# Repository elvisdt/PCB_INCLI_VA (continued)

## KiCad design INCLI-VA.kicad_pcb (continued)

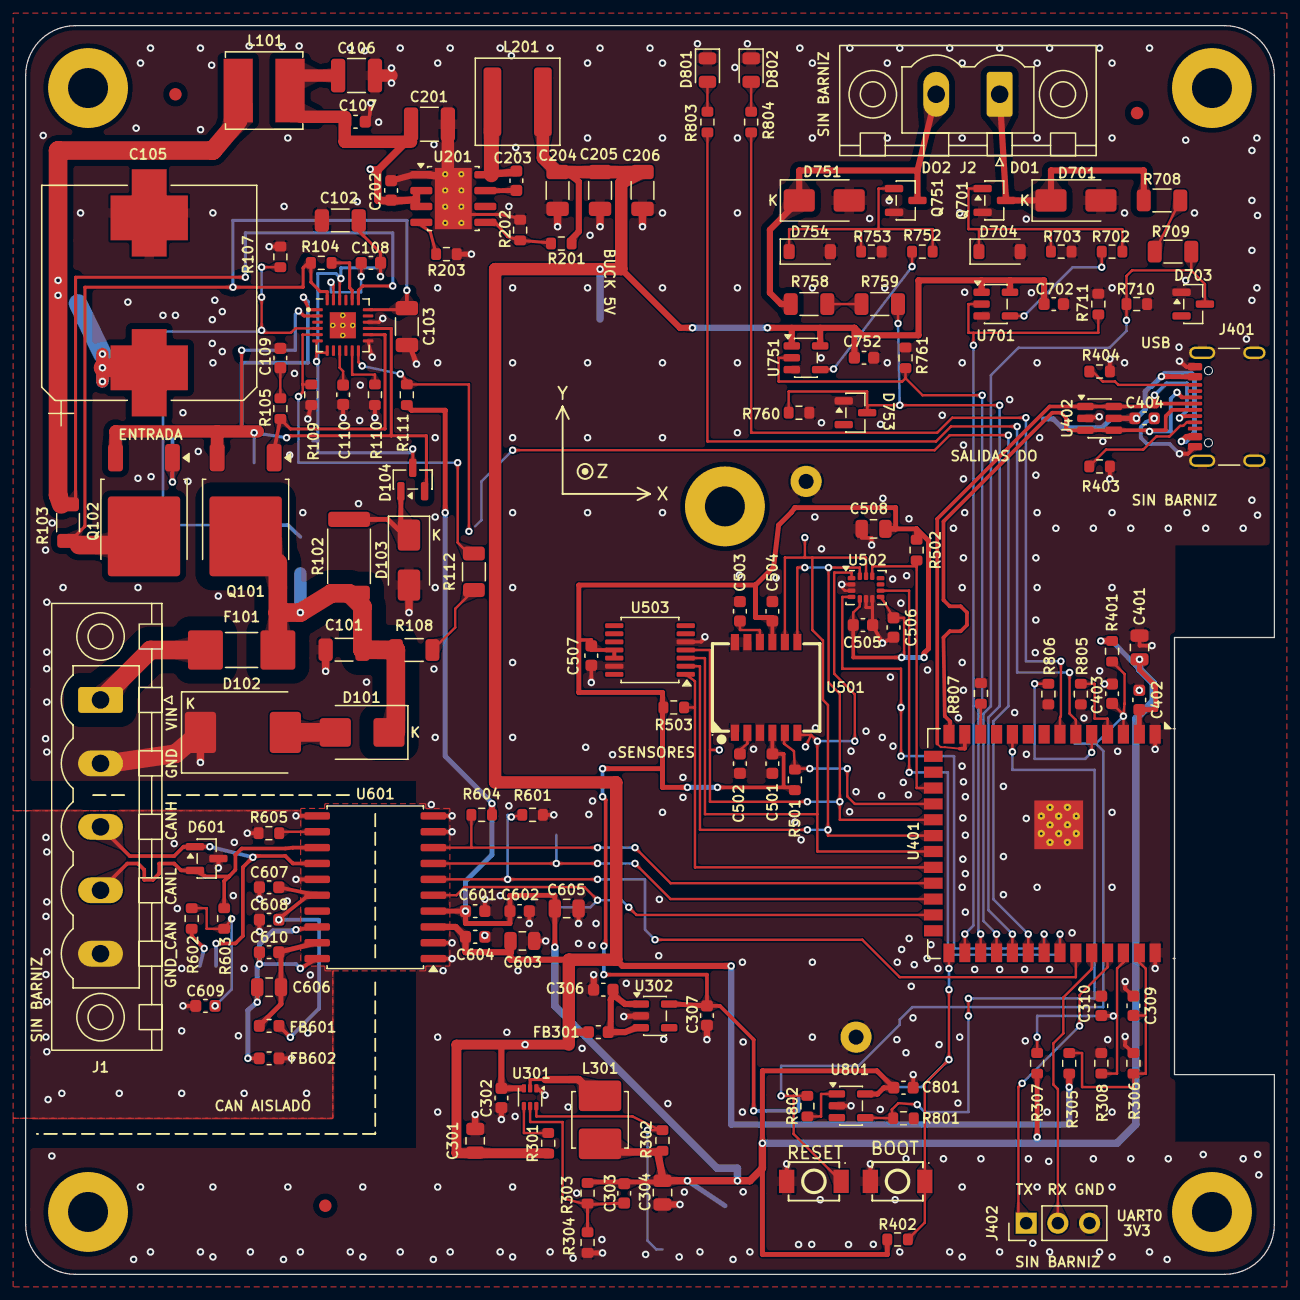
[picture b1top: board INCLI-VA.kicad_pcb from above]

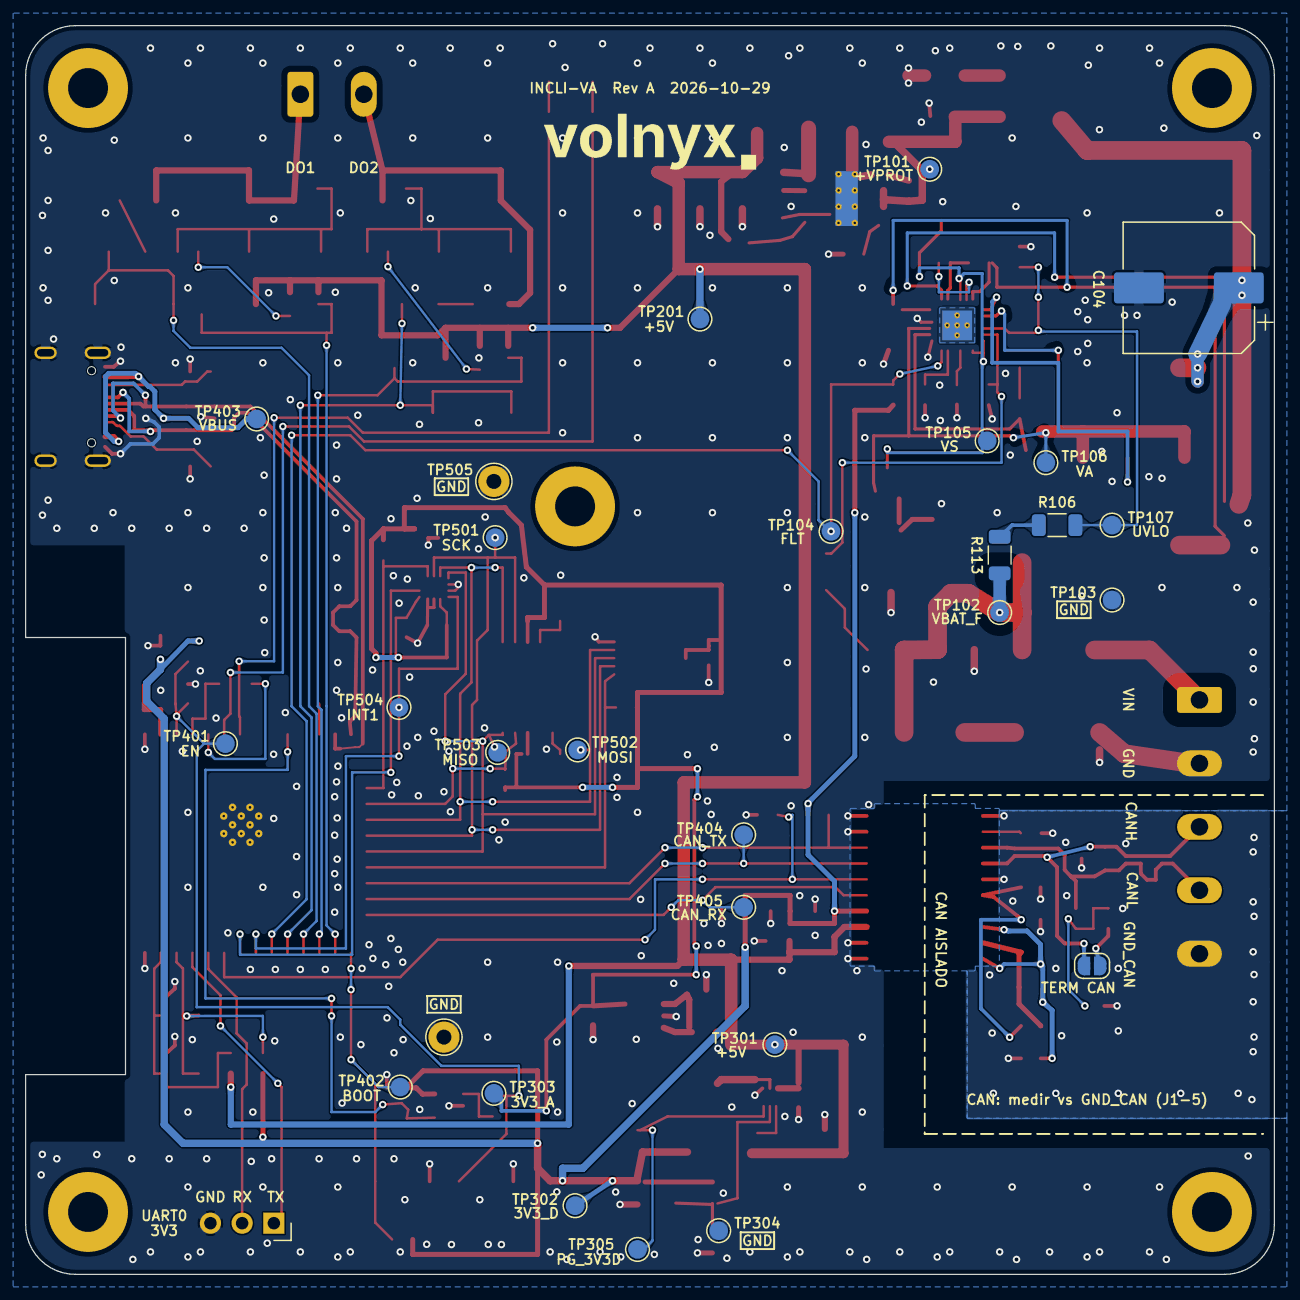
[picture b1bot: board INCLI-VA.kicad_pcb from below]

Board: 2 copper layers, 100.0 x 100.0 mm, 180 parts (29 on the bottom side), 89 nets.

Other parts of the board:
LOGO1: Logo_Volnyx_Wordmark

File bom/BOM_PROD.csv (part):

Comment,Designator,Footprint,Qty,MPN,Manufacturer,LCSC,JLC_Type,JLC_Stock,LCSC_Stock,Price_10_USD,Supplier,Assembly,Status,Orig_MPN,Orig_LCSC,Notes
100nF,C101,C_1206_3216Metric,1,CGA5L4X7T2W104K160AA,TDK,,,,,0.7901 (ref. LCSC),DigiKey/Mouser,consigna JLC o mano,"not at JLC, DigiKey/Mouser, checked 2026-10-30",,C3887150,PROD mantiene el AEC-Q200 original (JLC/LCSC stock 1); el sustituto sin AEC-Q200 es solo para PROTO
1uF,"C102,C103",C_1206_3216Metric,2,CL31B105KCHNNNE,Samsung,C13832,ext,347728,261400,0.0650,JLC,JLC,"substitute CL31B105KCHNNNE for CGA5L2X7R2A105K160AA accepted 2026-10-30, JLC ext",CGA5L2X7R2A105K160AA,C2168321,"original stock 0; 1uF 100V X7R 1206, no AEC-Q200"
47uF,C104,CP_Elec_10x10,1,EEE-HA2A470UP,Panasonic,,,,,0.3957 (ref. LCSC),DigiKey/Mouser,consigna JLC o mano,"not at JLC, DigiKey/Mouser, checked 2026-10-30",,C344077,PROD mantiene el AEC-Q200 original (JLC/LCSC stock 1); el sustituto sin AEC-Q200 es solo para PROTO
1000uF 50V,C105,CP_Elec_Panasonic_J16_VibProof,1,EEE-FK1H102AV,Panasonic,,,,,0.8694 (ref. LCSC),DigiKey/Mouser,consigna JLC o mano,"not at JLC, DigiKey/Mouser, checked 2026-10-30",,C2164039,JLC/LCSC stock 0 (tambien Alt_MPN EEE-FK1H102AM)
10uF,C106,C_1210_3225Metric,1,CL32B106KBJNNNE,Samsung,C138687,ext,101468,9473,0.2610,JLC,JLC,"substitute CL32B106KBJNNNE for GCM32ER71H106KA12L accepted 2026-10-30, JLC ext",GCM32ER71H106KA12L,,original no listado en JLC; 10uF 50V X7R 1210. Alternativa automotriz: C126612 GCM32EC71H106KA03L (X7S)
100nF,"C107,C108,C109,C202,C203,C302,C309,C310,C402,C404,C501,C502,C503,C504,C505,C506,C507,C602,C604,C608,C702,C752,C801",C_0603_1608Metric,23,GCM188R72A104KA64D,Murata,C415406,ext,15215,10480,0.0637,JLC,JLC,"consolidado 2026-10-30: un solo MPN de 100 nF, 100 V X7R AEC-Q200",,,"100nF 50V X7R 0603, no AEC-Q200"
68nF,C110,C_0603_1608Metric,1,CL10B683KB8NNNC,Samsung,C31658,pref,150525,115600,0.0190 (MOQ 50),JLC,JLC,"substitute CL10B683KB8NNNC for GCM188R71H683KA57D accepted 2026-10-30, JLC pref",GCM188R71H683KA57D,C380380,original stock 0; 68nF 50V X7R 0603 (JLC pref)
4.7uF,C201,C_1210_3225Metric,1,CGA6M3X7S2A475K200AB,TDK,,,,,1.5766 (ref. LCSC),DigiKey/Mouser,consigna JLC o mano,"not at JLC, DigiKey/Mouser, checked 2026-10-30",,C2168848,PROD mantiene el AEC-Q200 original (JLC/LCSC stock 0); el sustituto sin AEC-Q200 es solo para PROTO
22uF,"C204,C205,C206",C_1206_3216Metric,3,GCM31CR71A226KE02L,Murata,C126598,ext,13053,11240,0.3296,JLC,JLC,"JLC ext, verified 2026-10-30",,,
10uF,"C301,C508,C603,C605,C606",C_0805_2012Metric,5,GCM21BR71A106KE22L,Murata,C126586,ext,9971,0,0.1029,JLC,JLC,"JLC ext, verified 2026-10-30",,,
10pF,C303,C_0603_1608Metric,1,CL10C100JB8NNNC,Samsung,C1634,basic,1212785,100,0.0061 (MOQ 100),JLC,JLC,"JLC basic (swap from GCM1885C1H100JA16D), verified 2026-10-30",GCM1885C1H100JA16D,C126542,original stock 0; 10pF 50V C0G 0603
22uF,"C304,C401",C_0805_2012Metric,2,GRM21BZ71A226ME15L,Murata,C907991,ext,166294,140195,0.3744,JLC,JLC,"JLC ext, verified 2026-10-30",,,
1uF,"C306,C307,C403",C_0603_1608Metric,3,GCM188R71C105KA64D,Murata,C161212,ext,33722,18280,0.0383 (MOQ 20),JLC,JLC,"JLC ext, verified 2026-10-30",,,
10nF,"C601,C607",C_0603_1608Metric,2,0603B103K500NT,FH,C57112,basic,5628260,28450,0.0098 (MOQ 50),JLC,JLC,"JLC basic (swap from GCM188R71H103KA37D), verified 2026-10-30",GCM188R71H103KA37D,C85863,"10nF 50V X7R 0603, no AEC-Q200"
4.7nF,C609,C_0603_1608Metric,1,GCM188R72A472KA37D,Murata,C426631,ext,16111,16100,0.0288 (MOQ 20),JLC,JLC,"JLC ext, verified 2026-10-30",,,
220nF,C610,C_0603_1608Metric,1,CL10B224KA8NNNC,Samsung,C21120,basic,1011962,394350,0.0094 (MOQ 50),JLC,JLC,"JLC basic (swap from GCM188R71E224KA55D), verified 2026-10-30",GCM188R71E224KA55D,C161217,"220nF 25V X7R 0603, no AEC-Q200"
ES2G,D101,D_SMB,1,ES2G-E3/52T,Vishay,C2927419,ext,8924,8920,0.1781,JLC,JLC,"JLC ext, verified 2026-10-30",,,
SMCJ33A,D102,D_SMC,1,SMCJ33A,Littelfuse,C438109,ext,26629,26625,0.1049,JLC,JLC,"JLC ext, verified 2026-10-30",,,
SMAJ51A,D103,D_SMA,1,SMAJ51A,Littelfuse,C366557,ext,5525,5520,0.0314 (MOQ 20),JLC,JLC,"JLC ext, verified 2026-10-30",,,
BAV23C,D104,SOT-23,1,"BAV23C,215",Nexperia,C282370,ext,0,0,"0.1158 (ref. LCSC, MOQ 5)",DigiKey/Mouser,consigna JLC o mano,"not at JLC/LCSC (stock 0), DigiKey/Mouser, checked 2026-10-30",,,rc6 R-02 (D1 de TI fig. 8-1 dentro de D104); PROD automotriz: evaluar BAV23CQ
SMAJ58A,"D701,D751",D_SMA,2,SMAJ58A,Littelfuse,C123816,ext,15859,15840,0.0456 (MOQ 20),JLC,JLC,"JLC ext, verified 2026-10-30",,,
BZX84-C3V3,"D703,D753",SOT-23,2,"BZX84-C3V3,215",Nexperia,C85087,ext,28154,28150,0.0180 (MOQ 50),JLC,JLC,"JLC ext, verified 2026-10-30",,,
12V,"D704,D754",D_SOD-123,2,MMSZ5242B-7-F,Diodes Incorporated,C500776,ext,97152,97150,0.0450,JLC,JLC,"JLC ext, verified 2026-10-30",,,
2A 250VDC,F101,Fuse_Bourns_SF-2410,1,SF-2410FPA200W-2,Bourns,,,,,1.0524 (ref. LCSC),DigiKey/Mouser,consigna JLC o mano,"not at JLC, DigiKey/Mouser, checked 2026-10-30",,C3159902,"JLC/LCSC stock 0; sustituto AEM MF2410 rechazado (proteccion de entrada, el prototipo valida el diseno de produccion)"
220R@100MHz,FB301,L_0603_1608Metric,1,BLM18PG221SN1D,Murata,C80165,ext,243305,235750,0.0149 (MOQ 50),JLC,JLC,"JLC ext, verified 2026-10-30",,,
1.8k@100MHz,"FB601,FB602",L_0603_1608Metric,2,BLM18BD182SN1D,Murata,C113020,ext,5170,5160,0.0362 (MOQ 20),JLC,JLC,"JLC ext, verified 2026-10-30",,,
"MSTBV 2,5/5-GF-5,08",J1,"PhoenixContact_MSTBV_2,5_5-GF-5,08_1x05_P5.08mm_Vertical_ThreadedFlange",1,1777109,Phoenix Contact,C7164734,ext,327,317,0.9724,LCSC,mano,"JLC ext, verified 2026-10-30",,,
"MSTBV 2,5/2-GF-5,08",J2,"PhoenixContact_MSTBV_2,5_2-GF-5,08_1x02_P5.08mm_Vertical_ThreadedFlange",1,1777073,Phoenix Contact,C480552,ext,837,835,1.1001,LCSC,mano,"JLC ext, verified 2026-10-30",,,
USB4105-GF-A,J401,USB_C_Receptacle_GCT_USB4105-xx-A_16P_TopMnt_Horizontal,1,USB4105-GF-A,GCT,C3020560,ext,3189,413,1.1001,LCSC,mano,"JLC ext, verified 2026-10-30",,,
UART0,J402,PinHeader_1x03_P2.54mm_Vertical,1,2.54-1*3PPin,BOOMELE,C49257,ext,151423,151440,0.0286 (MOQ 20),LCSC,mano,"substitute 2.54-1*3PPin for 61300311121 accepted 2026-10-30, JLC ext",61300311121,C2915006,"Wurth 61300311121 solo en JLC, no en lcsc.com; tira 1x3 2.54 mm generica"
10uH,L101,L_Bourns_SRN6045TA,1,SRN6045TA-100M,Bourns,C2046332,ext,6156,6045,0.2544,JLC,JLC,"JLC ext, verified 2026-10-30",,,
33uH,L201,L_Coilcraft_XAL6060-XXX,1,XAL6060-333MEC,Coilcraft,,,,,2.8281 (ref. LCSC),DigiKey/Mouser,consigna JLC o mano,"not at JLC, DigiKey/Mouser, checked 2026-10-30",,C5119929,JLC/LCSC stock 0; sin equivalente 33uH en la misma huella
1uH,L301,L_Coilcraft_XAL4020_HandSolder,1,XAL4020-102MEC,Coilcraft,C4555951,ext,7626,7626,4.2523,JLC,JLC,"JLC ext, verified 2026-10-30",,,
STD18NF25,Q101,TO-252-2,1,STD18NF25,STMicroelectronics,,,,,5.3743 (ref. LCSC),DigiKey/Mouser,consigna JLC o mano,"not at JLC, DigiKey/Mouser, checked 2026-10-30",,C183634,JLC/LCSC stock 0; sustituto AOD458 rechazado (proteccion de entrada)
IPD30N10S3L-34,Q102,TO-252-2,1,IPD30N10S3L34ATMA1,Infineon,,,,,1.2069 (ref. LCSC),DigiKey/Mouser,consigna JLC o mano,"not at JLC, DigiKey/Mouser, checked 2026-10-30",,C148263,JLC/LCSC stock 0; sustituto IRLR3110Z rechazado (proteccion de entrada)
DMN10H220LQ,"Q701,Q751",SOT-23,2,DMN10H220LQ-7,Diodes Incorporated,C5260572,ext,4738,4595,0.2997,JLC,JLC,"JLC ext, verified 2026-10-30",,,
10k,R102,R_2512_6332Metric,1,AC2512FK-0710KL,Yageo,C469651,ext,1508,1505,0.0933,JLC,JLC,"JLC ext, verified 2026-10-30",,,
10m,R103,R_1206_3216Metric,1,ERJ-8BWFR010V,Panasonic,C2076185,ext,5332,4125,0.1219,JLC,JLC,"JLC ext, verified 2026-10-30",,,
49.9,R104,R_0603_1608Metric,1,0603WAF499JT5E,UNI-ROYAL,C23185,basic,1388908,411400,0.0021 (MOQ 100),JLC,JLC,"JLC basic (swap from AC0603FR-0749R9L), verified 2026-10-30",AC0603FR-0749R9L,C144653,1% 0603
100,R105,R_0603_1608Metric,1,0603WAF1000T5E,UNI-ROYAL,C22775,basic,9522722,1107900,0.0024 (MOQ 100),JLC,JLC,"JLC basic (swap from AC0603FR-07100RL), verified 2026-10-30",AC0603FR-07100RL,C125923,1% 0603
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
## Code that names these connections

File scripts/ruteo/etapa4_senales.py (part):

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P = '/10_power_input/'
# SW: pin 3 -> R106.1 recto al oeste.
T(P+'SW', .2, [(123.375, 73.75), (120.4, 73.75)])
# UVLO: pin 4 -> oeste por el hueco R106/C109 -> x118.9 -> R106.2; salto B.Cu
# bajo la Kelvin C_ID (y70.95) hasta R107.1.
T(P+'UVLO', .2, [(123.375, 74.25), (121.6, 74.25), (121.25, 74.6), (118.9, 74.6), (118.9, 71.745), (120.4, 71.745)])
V(P+'UVLO', (118.9, 71.745))
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# TMR, ILIM.
T(P+'TMR', .2, [(125.15, 76.025), (125.15, 77.4), (125.425, 77.675), (125.425, 78.785)])
T(P+'ILIM', .2, [(126.15, 76.025), (126.15, 77.95), (127.975, 77.95), (127.975, 78.735)])
# FLT: pin 12 -> via -> B.Cu bajo HGATE/VA -> R111.2 -> TP104.
FLT = '/PWR_FLT_N'
T(FLT, .2, [(126.65, 76.025), (126.65, 76.95), (126.95, 77.25)])
V(FLT, (126.95, 77.25))
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V(VS, (128.42, 70.1))
T(VS, .25, [(128.42, 70.1), (128.425, 69.0)])
T(VS, .25, [(128.425, 69.0), (128.425, 68.2), (126.675, 66.45), (126.675, 65.6)])
# CAP: pin 23 -> via -> U por B.Cu y71.35 -> via -> C108.1.
CAP = P+'CAP'
T(CAP, .2, [(124.65, 71.975), (124.65, 70.75), (124.45, 70.55)])
V(CAP, (124.45, 70.55))
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T('/VAR_ID1', .2, [(180.8, 102.7), (181.9, 102.705)])

# ---------------------------------------------- Bus bajo el modulo y USB ----
# Pines 28-32 (DO1_EN, DO2_EN, DO1_DIAG, DO2_DIAG, PWR_FLT_N) bajan a B.Cu en el
# lado interior del pad y suben por carriles x175.9-177.5; LED_G/LED_R se suman
# en el bolsillo norte. Todos cruzan el par USB una sola vez, por B.Cu.
bus = [('/DO1_EN', 175.21), ('/DO2_EN', 176.48), ('/DO1_DIAG', 177.75), ('/DO2_DIAG', 179.02), (FLT, 180.29)]
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M('R502', (171.35, 92.0), 270)
M('TP504', (170.1, 104.6), 180)

# --- CS_IMU: pin 17 -> x171.35 -> norte -> pad 12; R502 en el camino ---
CSI = '/CS_IMU'
T(CSI, .2, [(172.69, 111.055), (171.35, 111.055), (171.35, 93.3), (167.8, 93.3), (167.8, 94.0875)])
T(CSI, .2, [(171.35, 93.3), (171.35, 92.825)])
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T(SCK, .2, [(162.6, 114.4), (164.25, 114.4)], B); V(SCK, (164.25, 114.4))                                         # cruce J_e (via en la banda)
T(CSR, .2, [(152.8625, 101.95), (153.6, 102.5), (153.6, 117.405), (172.69, 117.405)])
T(CSR, .2, [(152.725, 104.6), (153.6, 104.6)])
# CS_INC: pin 18 -> salto bajo MOSI/SCK/MISO (J_c) -> R501 -> U501.5
T(CSN, .2, [(172.69, 112.325), (166.4, 112.325), (165.8, 111.725), (165.8, 109.5)]); V(CSN, (165.8, 109.5))
T(CSN, .2, [(165.8, 109.5), (162.8, 109.5)], B); V(CSN, (162.8, 109.5))
T(CSN, .2, [(162.8, 109.5), (161.6, 109.5), (161.6, 109.575)])
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
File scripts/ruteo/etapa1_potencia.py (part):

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    'VP': '+VPROT', 'G': 'GND_VEH', 'SW': '/20_buck_5v/BUCK_SW', 'BOOT': '/20_buck_5v/BUCK_BOOT',
    'FB': '/20_buck_5v/BUCK_FB', 'RT': '/20_buck_5v/BUCK_RT', 'P5': '+5V_VEH', 'A1': 'Net-(D103-A1)',
    'SW3': 'Net-(U301-SW)', 'FB3': 'Net-(U301-FB)', 'EN3': 'Net-(U301-EN)', 'UEN': 'Net-(U302-EN)',
    'P3D': '+3V3_D', 'P3A': '+3V3_A', 'PG3': '/30_regulation/PG_3V3D',
}


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T('VOUT', 1.0, [(106.15, 76.3), (106.15, 78.5)], B)
T('VOUT', 1.5, [(106.15, 76.3), (104.2, 72.25)], B)

# Kelvin de R103: dos pistas separadas desde los pads hasta U101 (CSP via R104 y CS- pin 19).
T('VOUT', 0.25, [(104.0, 88.1), (104.0, 70.15), (117.6, 70.15)])
V('VOUT', 117.6, 70.15)
T('CID', 0.25, [(104.0, 90.85), (104.75, 90.1), (104.75, 70.95), (122.3, 70.95), (122.3, 69.4), (122.6, 69.0)])
V('CID', 116.6, 70.95)
# CS- (pin 19): F.Cu corto hasta una via y arco por B.Cu hasta la Kelvin VOUT.
T('VOUT', 0.25, [(126.65, 71.9), (126.65, 71.2), (127.0, 70.85), (129.4, 70.85)])
V('VOUT', 129.4, 70.85)
T('VOUT', 0.25, [(129.4, 70.85), (129.4, 66.6), (117.6, 66.6), (117.6, 70.15)], B)
# CS+ (pin 20) -> R104.1
T('CSP', 0.25, [(126.15, 71.9), (126.15, 71.2), (125.95, 71.0), (125.95, 69.0), (124.5, 69.0)])
# C (pin 24) -> R104.2; ISCP (pin 18) -> C103.1 -> via -> arco B.Cu exterior -> Kelvin C_ID.
T('CID', 0.25, [(124.15, 71.9), (124.15, 71.3), (123.6, 71.3), (122.85, 70.55), (122.85, 69.0)])
T('CID', 0.25, [(127.6, 72.75), (129.8, 72.75)])
T('CID', 0.3, [(130.53, 72.3), (130.53, 71.2)])
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T('G', 0.4, [(130.9, 76.0), (131.3, 77.1)])
V('G', 131.3, 77.1)                                        # C103.2

# DGATE: gate de Q102 -> via -> B.Cu por debajo del retorno VA (pin A -> tronco VA): lazo minimo.
T('DG', 0.3, [(111.76, 84.6), (111.76, 86.55)])
V('DG', 111.76, 86.55)
T('DG', 0.3, [(111.76, 86.55), (111.76, 82.5), (117.3, 82.5), (117.3, 77.0), (122.6, 77.0),
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T('VA', 0.25, [(121.85, 72.85), (121.6, 73.1), (121.6, 76.0), (117.3, 76.0)], B)
V('VA', 117.3, 76.0)
T('VA', 0.25, [(117.3, 76.0), (117.3, 82.5)])
# OUT (pin 15) y HGATE (pin 14) en paralelo (0.5 mm entre ejes) por el pasillo entre U101 y C103 y por el
# sur de la fila R109-R111; OUT salta por B.Cu sobre el enlace R105-Q101 hasta el tronco VA.
T('VA', 0.25, [(127.6, 74.25), (129.28, 74.25), (129.28, 82.85), (121.2, 82.85), (120.9, 83.0)])
V('VA', 120.9, 83.0)
T('VA', 0.25, [(120.9, 83.0), (118.3, 82.6)], B)
V('VA', 118.3, 82.6)
# HGATE: gate de Q101 <-> R105 <-> pin 14 por el sur de la fila R109-R111.
T('HG', 0.3, [(119.9, 84.0), (120.4, 81.5)])
T('HG', 0.25, [(120.4, 81.5), (121.2, 82.3), (128.78, 82.3), (128.78, 74.75), (127.6, 74.75)])

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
